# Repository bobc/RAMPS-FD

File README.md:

# RAMPS-FD

RAMPS for Due.

THIS IS THE DEVELOPMENT BRANCH.

Design files in the development branch are untested and not ready for manufacturing.

Status
-------

Nothing is ready for release yet!

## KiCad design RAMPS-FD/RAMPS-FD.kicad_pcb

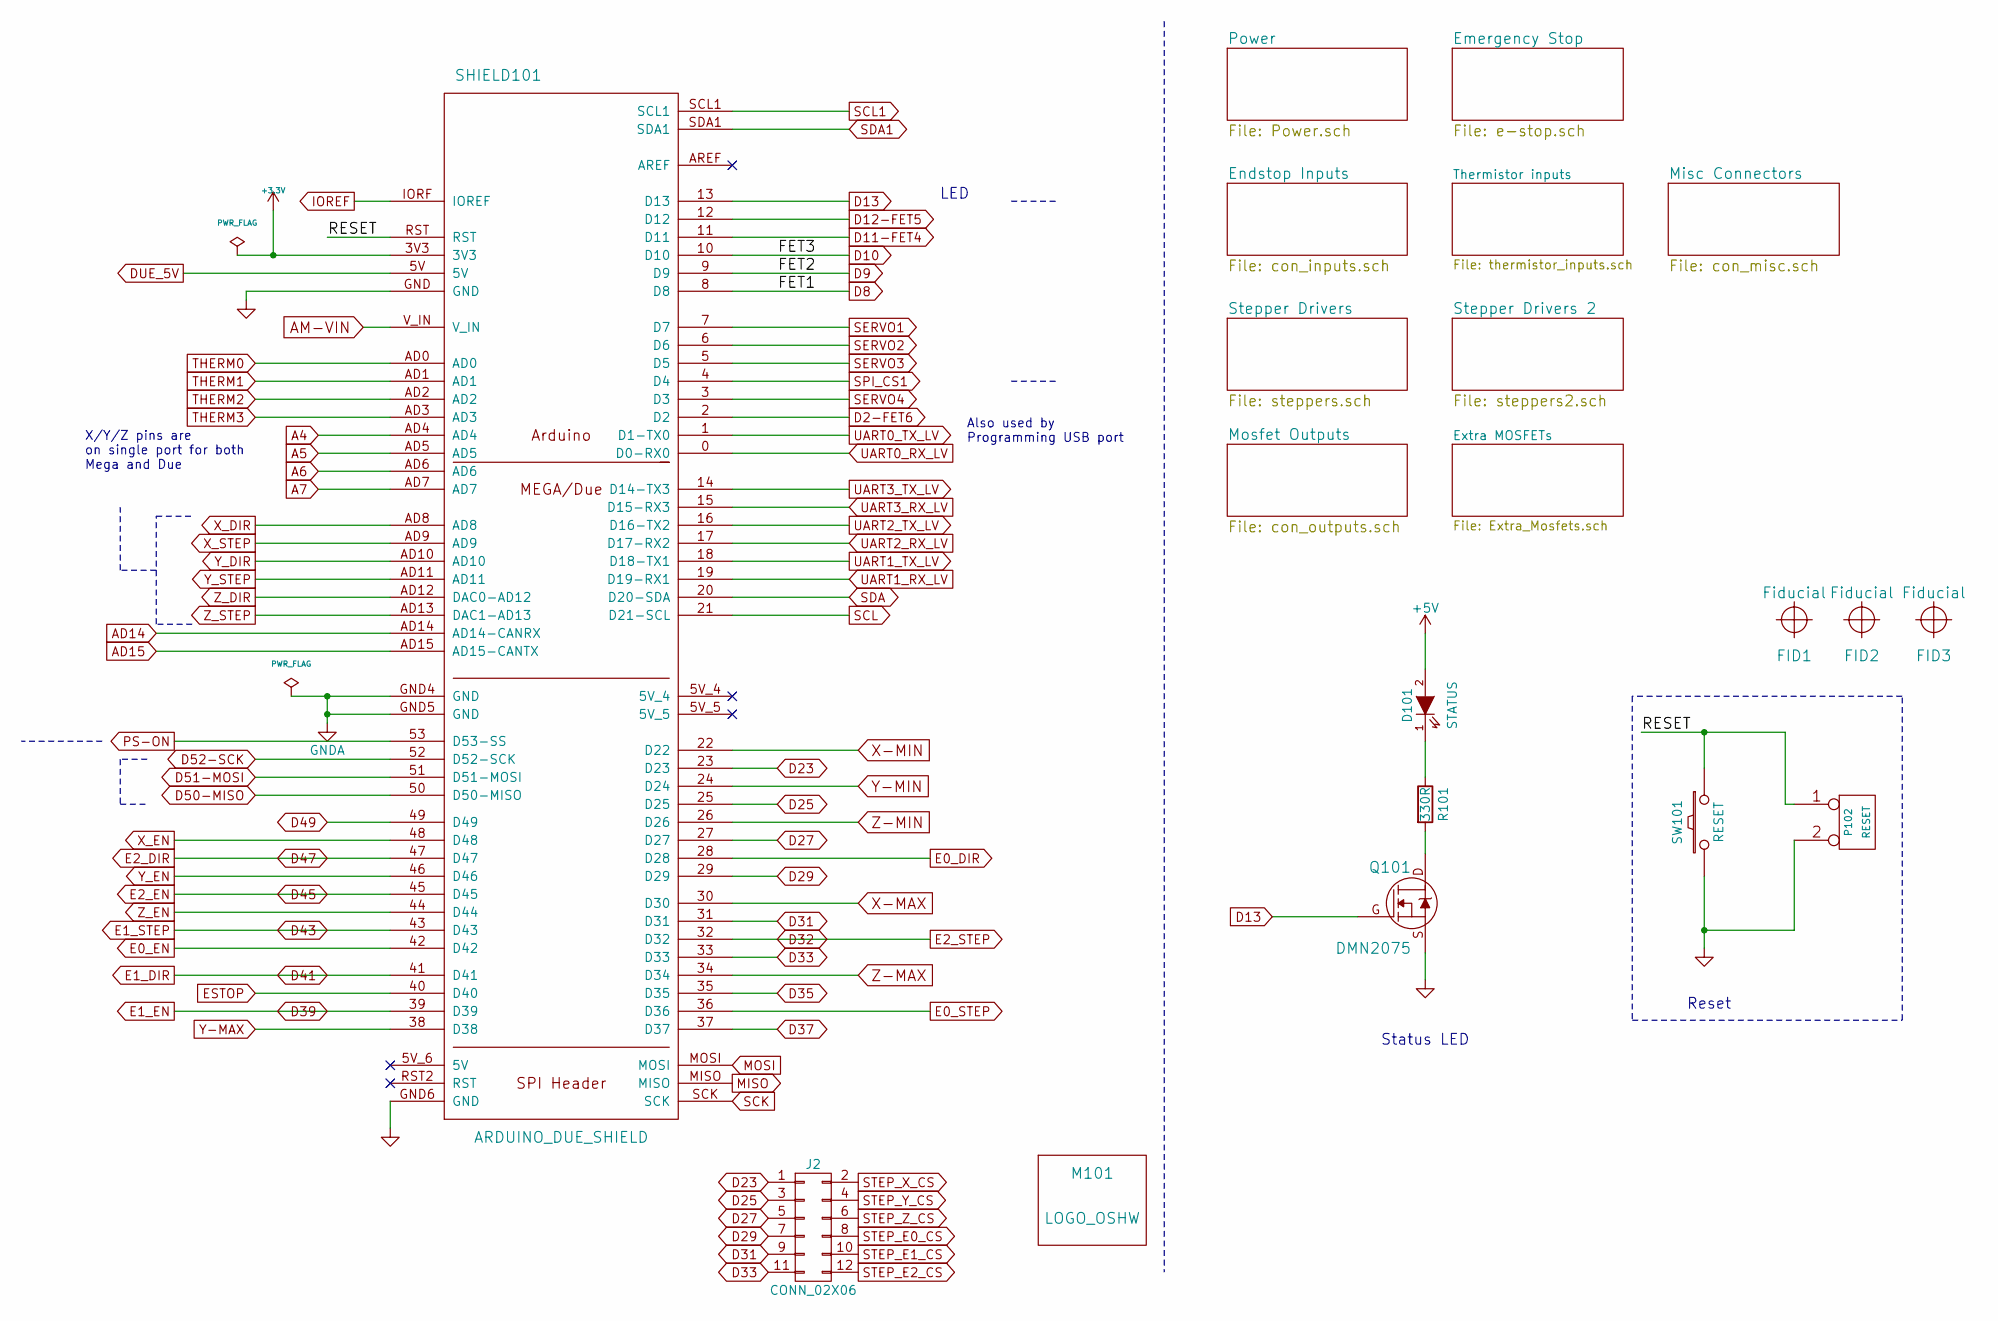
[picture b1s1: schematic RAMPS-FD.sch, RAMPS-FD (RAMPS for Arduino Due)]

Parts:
D101: STATUS; LED-0805_GREEN
FID1, FID2, FID3: Fiducial; Fiducial_1mm_Dia_2.54mm_Outer_CopperTop
J2: CONN_02X06; Pin_Header_Straight_2x06_Pitch2.54mm
M101: LOGO_OSHW; OSHW_logo_2
P102: RESET; Pin_Header_Straight_1x02_Pitch2.54mm
Q101: DMN2075; SOT23GDS
R101: 330R; R_0603
SHIELD101: ARDUINO_DUE_SHIELD; ARDUINO_MEGA_DUE_SHIELD_FOOTPRINT_RMC
SW101: RESET; SW_6x6_SMD

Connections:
+5V: D101.2 (A); also elsewhere on the board
/RESET: P102.1, SHIELD101.RST, SW101.1
A4: SHIELD101.AD4; also elsewhere on the board
A5: SHIELD101.AD5; also elsewhere on the board
A6: SHIELD101.AD6; also elsewhere on the board
A7: SHIELD101.AD7; also elsewhere on the board
AD14: SHIELD101.AD14 (AD14-CANRX); also elsewhere on the board
AD15: SHIELD101.AD15 (AD15-CANTX); also elsewhere on the board
AM-VIN: SHIELD101.V_IN; also elsewhere on the board
D2-FET6: SHIELD101.2 (D2); also elsewhere on the board
D8: SHIELD101.8 (D8); also elsewhere on the board
D9: SHIELD101.9 (D9); also elsewhere on the board
D10: SHIELD101.10 (D10); also elsewhere on the board
D11-FET4: SHIELD101.11 (D11); also elsewhere on the board
D12-FET5: SHIELD101.12 (D12); also elsewhere on the board
D13: Q101.G, SHIELD101.13 (D13)
D23: J2.1, SHIELD101.23 (D23); also elsewhere on the board
D25: J2.3, SHIELD101.25 (D25); also elsewhere on the board
D27: J2.5, SHIELD101.27 (D27); also elsewhere on the board
D29: J2.7, SHIELD101.29 (D29); also elsewhere on the board
D31: J2.9, SHIELD101.31 (D31); also elsewhere on the board
D32: SHIELD101.32 (D32); also elsewhere on the board
D33: J2.11, SHIELD101.33 (D33); also elsewhere on the board
D35: SHIELD101.35 (D35); also elsewhere on the board
D37: SHIELD101.37 (D37); also elsewhere on the board
D39: SHIELD101.39 (D39); also elsewhere on the board
D41: SHIELD101.41 (D41); also elsewhere on the board
D43: SHIELD101.43 (D43); also elsewhere on the board
D45: SHIELD101.45 (D45); also elsewhere on the board
D47: SHIELD101.47 (D47); also elsewhere on the board
D49: SHIELD101.49 (D49); also elsewhere on the board
D50-MISO: SHIELD101.50 (D50-MISO); also elsewhere on the board
D51-MOSI: SHIELD101.51 (D51-MOSI); also elsewhere on the board
D52-SCK: SHIELD101.52 (D52-SCK); also elsewhere on the board
DUE_5V: SHIELD101.5V; also elsewhere on the board
E0_DIR: SHIELD101.28 (D28); also elsewhere on the board
E0_EN: SHIELD101.42 (D42); also elsewhere on the board
E0_STEP: SHIELD101.36 (D36); also elsewhere on the board
ESTOP: SHIELD101.40 (D40); also elsewhere on the board
GND: P102.2 (PM), Q101.S, SHIELD101.GND, SHIELD101.GND6 (GND), SW101.2; also elsewhere on the board
GNDA: SHIELD101.GND4 (GND), SHIELD101.GND5 (GND); also elsewhere on the board
IOREF: SHIELD101.IORF (IOREF); also elsewhere on the board
MISO: SHIELD101.MISO; also elsewhere on the board
MOSI: SHIELD101.MOSI; also elsewhere on the board
unnamed: D101.1 (K), R101.1
unnamed: Q101.D, R101.2
PS-ON: SHIELD101.53 (D53-SS); also elsewhere on the board
SCK: SHIELD101.SCK; also elsewhere on the board
SCL: SHIELD101.21 (D21-SCL); also elsewhere on the board
SCL1: SHIELD101.SCL1; also elsewhere on the board
SDA: SHIELD101.20 (D20-SDA); also elsewhere on the board
SDA1: SHIELD101.SDA1; also elsewhere on the board
SERVO1: SHIELD101.7 (D7); also elsewhere on the board
SERVO2: SHIELD101.6 (D6); also elsewhere on the board
SERVO3: SHIELD101.5 (D5); also elsewhere on the board
SERVO4: SHIELD101.3 (D3); also elsewhere on the board
SPI_CS1: SHIELD101.4 (D4); also elsewhere on the board
THERM0: SHIELD101.AD0; also elsewhere on the board
THERM1: SHIELD101.AD1; also elsewhere on the board
THERM2: SHIELD101.AD2; also elsewhere on the board
THERM3: SHIELD101.AD3; also elsewhere on the board
UART0_RX_LV: SHIELD101.0 (D0-RX0); also elsewhere on the board
UART0_TX_LV: SHIELD101.1 (D1-TX0); also elsewhere on the board
UART1_RX_LV: SHIELD101.19 (D19-RX1); also elsewhere on the board
UART1_TX_LV: SHIELD101.18 (D18-TX1); also elsewhere on the board
UART2_RX_LV: SHIELD101.17 (D17-RX2); also elsewhere on the board
UART2_TX_LV: SHIELD101.16 (D16-TX2); also elsewhere on the board
UART3_RX_LV: SHIELD101.15 (D15-RX3); also elsewhere on the board
UART3_TX_LV: SHIELD101.14 (D14-TX3); also elsewhere on the board
X-MAX: SHIELD101.30 (D30); also elsewhere on the board
X-MIN: SHIELD101.22 (D22); also elsewhere on the board
X_DIR: SHIELD101.AD8; also elsewhere on the board
X_EN: SHIELD101.48 (D48); also elsewhere on the board
X_STEP: SHIELD101.AD9; also elsewhere on the board
Y-MAX: SHIELD101.38 (D38); also elsewhere on the board
Y-MIN: SHIELD101.24 (D24); also elsewhere on the board
Y_DIR: SHIELD101.AD10; also elsewhere on the board
Y_EN: SHIELD101.46 (D46); also elsewhere on the board
Y_STEP: SHIELD101.AD11; also elsewhere on the board
Z-MAX: SHIELD101.34 (D34); also elsewhere on the board
Z-MIN: SHIELD101.26 (D26); also elsewhere on the board
Z_DIR: SHIELD101.AD12 (DAC0-AD12); also elsewhere on the board
Z_EN: SHIELD101.44 (D44); also elsewhere on the board
Z_STEP: SHIELD101.AD13 (DAC1-AD13); also elsewhere on the board

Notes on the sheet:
Also used by Programming USB port
X/Y/Z pins are on single port for both Mega and Due
Reset
Status LED
LED

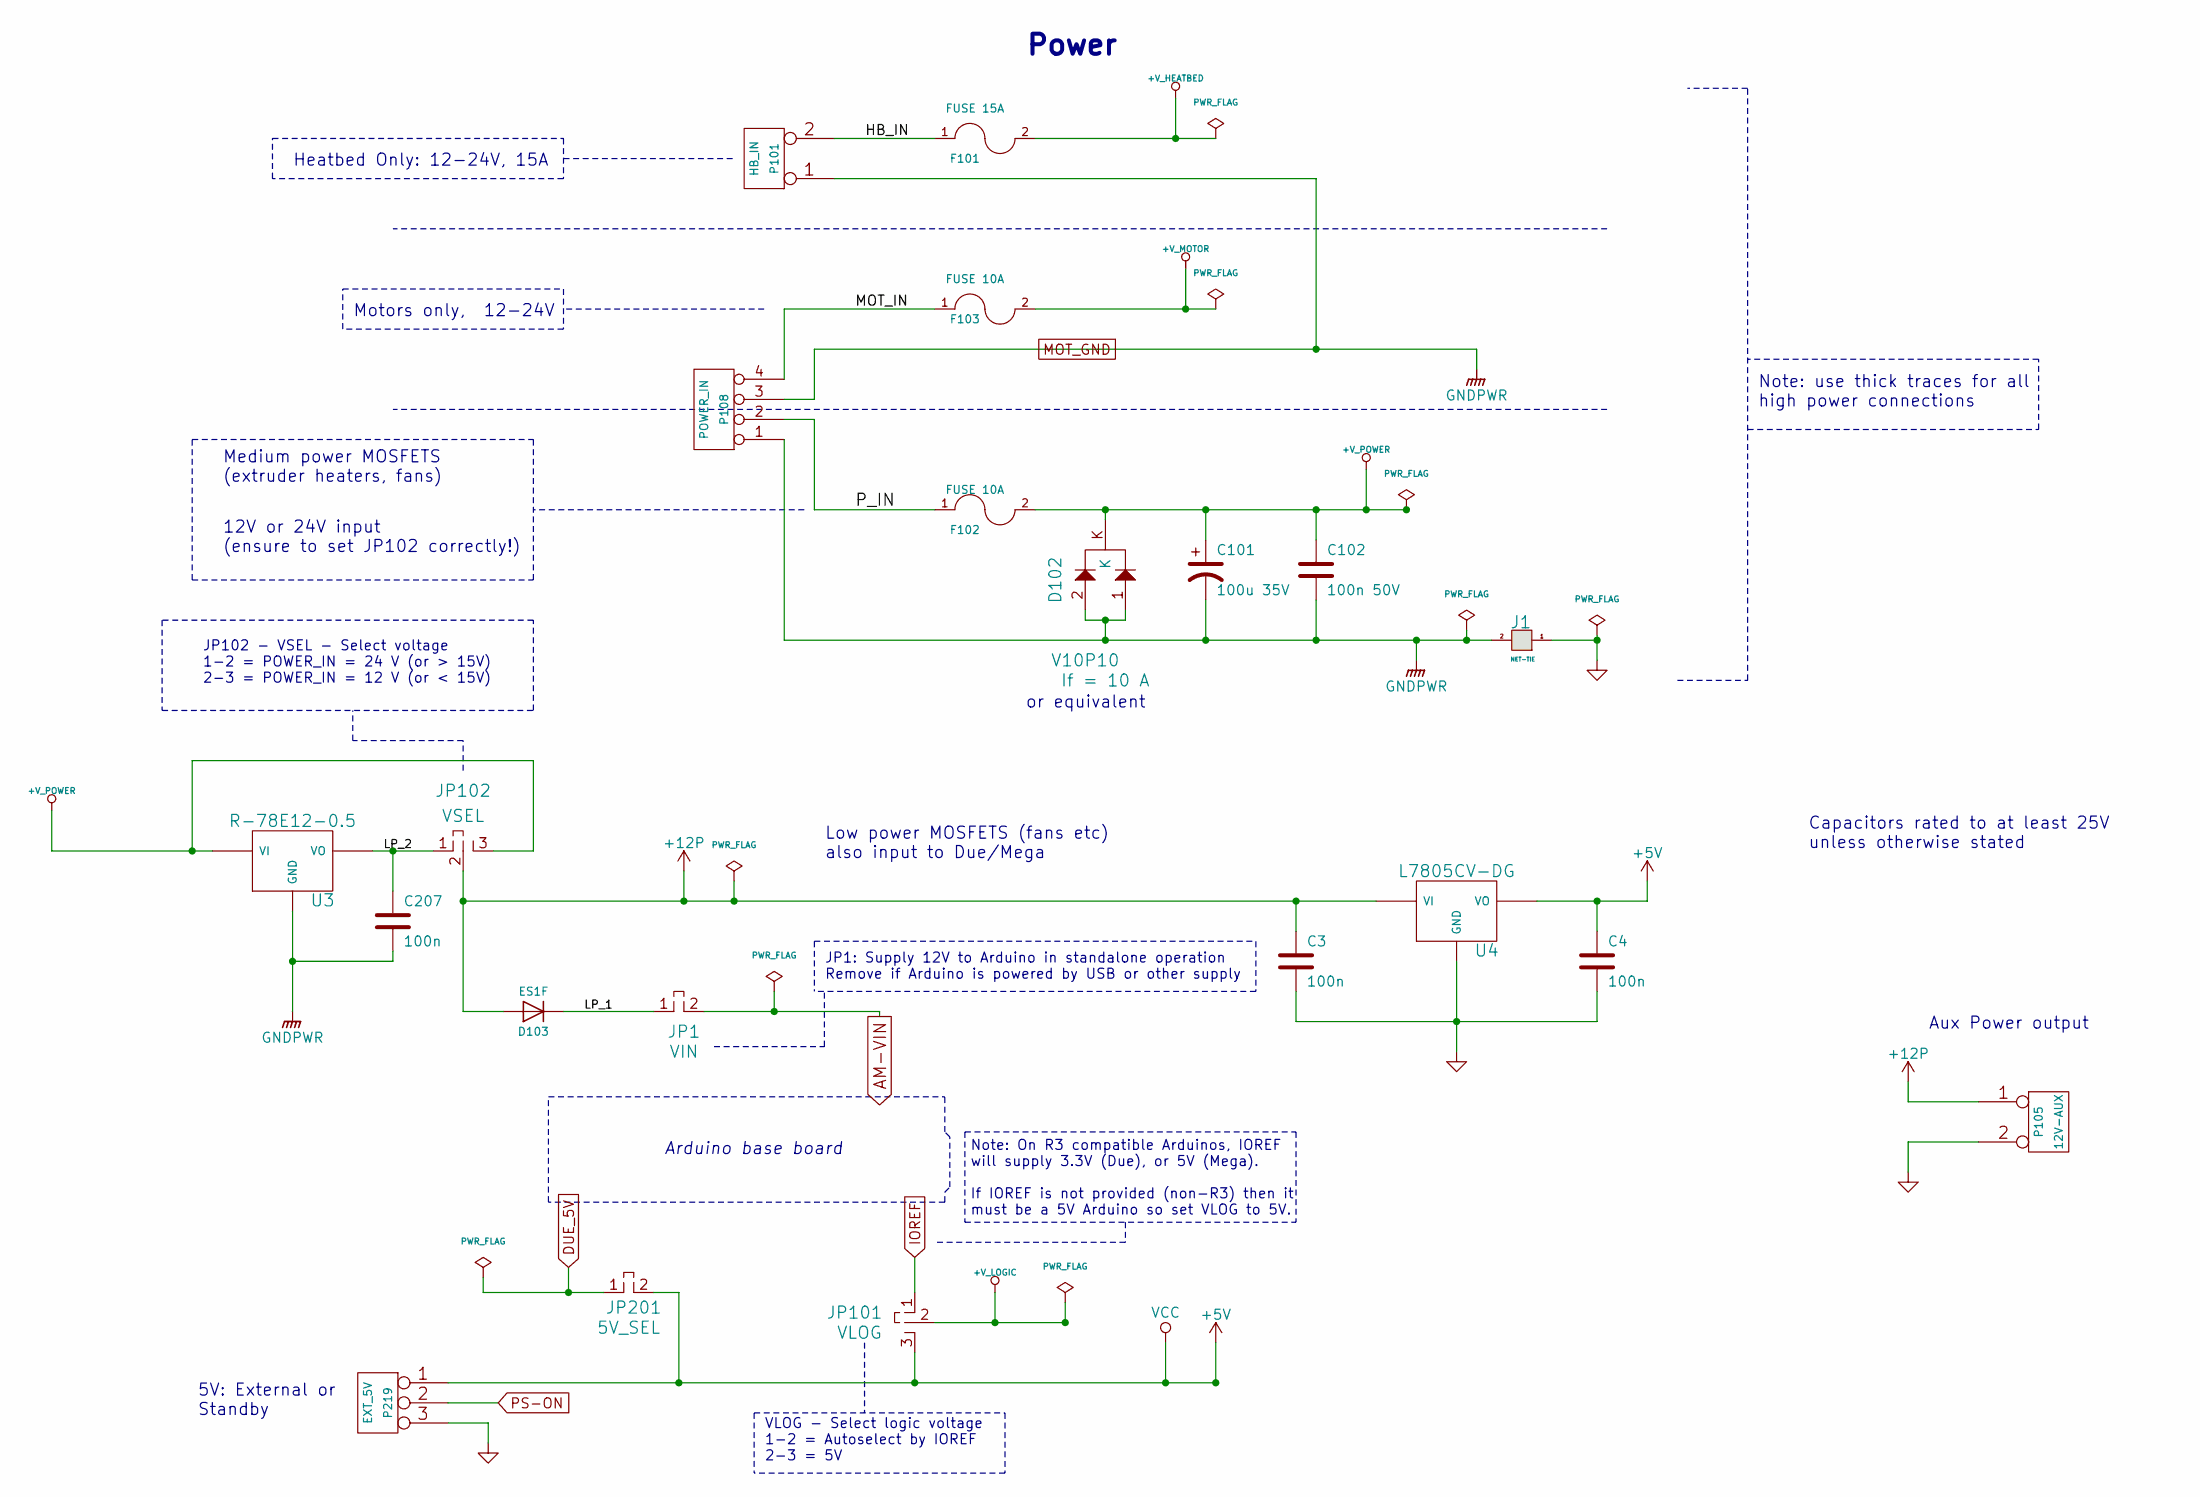
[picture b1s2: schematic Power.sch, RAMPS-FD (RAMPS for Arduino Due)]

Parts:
C3, C4, C207: 100n; C_0603
C101: 100u 35V; CP_Elec_6.3x7.7
C102: 100n 50V; C_0603
D102: V10P10; TO277A_RMC
D103: ES1F; DO-214AC
F101: FUSE 15A; Keystone_3568
F102, F103: FUSE 10A; Keystone_3568
J1: NET-TIE; TIE-1MM
JP1: VIN; Pin_Header_Straight_1x02_Pitch2.54mm
JP101: VLOG; Pin_Header_Straight_1x03_Pitch2.54mm
JP102: VSEL; Pin_Header_Straight_1x03_Pitch2.54mm
JP201: 5V_SEL; Pin_Header_Straight_1x02_Pitch2.54mm
P101: HB_IN; mstba_2,5%2f2-g-5,08
P105: 12V-AUX; CONN_KK_2.54_2W
P108: POWER_IN; mstba_2,5%2f4-g-5,08
P219: EXT_5V; CONN_KK_2.54_3W
U3: R-78E12-0.5; LM78XXV
U4: L7805CV-DG; LM78XXV

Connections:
+5V: C4.1, JP101.3, JP201.2, P219.1, U4.VO; also elsewhere on the board
+12P: C3.1, D103.2 (A), JP102.2, P105.1, U4.VI; also elsewhere on the board
+V_HEATBED: F101.2; also elsewhere on the board
+V_LOGIC: JP101.2; also elsewhere on the board
+V_MOTOR: F103.2; also elsewhere on the board
+V_POWER: C101.1, C102.1, D102.K, F102.2, JP102.3, U3.VI; also elsewhere on the board
/Power/HB_IN: F101.1, P101.2 (PM)
/Power/LP_1: D103.1 (K), JP1.1
/Power/LP_2: C207.1, JP102.1, U3.VO
/Power/MOT_IN: F103.1, P108.4
/Power/P_IN: F102.1, P108.2
AM-VIN: JP1.2; also elsewhere on the board
DUE_5V: JP201.1; also elsewhere on the board
GND: C3.2, C4.2, J1.1, P105.2 (PM), P219.3, U4.GND; also elsewhere on the board
IOREF: JP101.1; also elsewhere on the board
MOT_GND: C101.2, C102.2, C207.2, D102.1, D102.2, J1.2, P101.1, P108.1, P108.3, U3.GND; also elsewhere on the board
PS-ON: P219.2 (PM); also elsewhere on the board

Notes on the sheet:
JP102 - VSEL - Select voltage 1-2 = POWER_IN = 24 V (or > 15V) 2-3 = POWER_IN = 12 V (or < 15V)
Low power MOSFETS (fans etc) also input to Due/Mega
Aux Power output
VLOG - Select logic voltage 1-2 = Autoselect by IOREF 2-3 = 5V
Medium power MOSFETS (extruder heaters, fans)
Heatbed Only: 12-24V, 15A
Motors only, 12-24V
Power
JP1: Supply 12V to Arduino in standalone operation Remove if Arduino is powered by USB or other supply
Note: use thick traces for all high power connections
12V or 24V input (ensure to set JP102 correctly!)
5V: External or Standby
or equivalent
Arduino base board
Note: On R3 compatible Arduinos, IOREF will supply 3.3V (Due), or 5V (Mega). If IOREF is not provided (non-R3) then it must be a 5V Arduino so set VLOG to 5V.
Capacitors rated to at least 25V unless otherwise stated

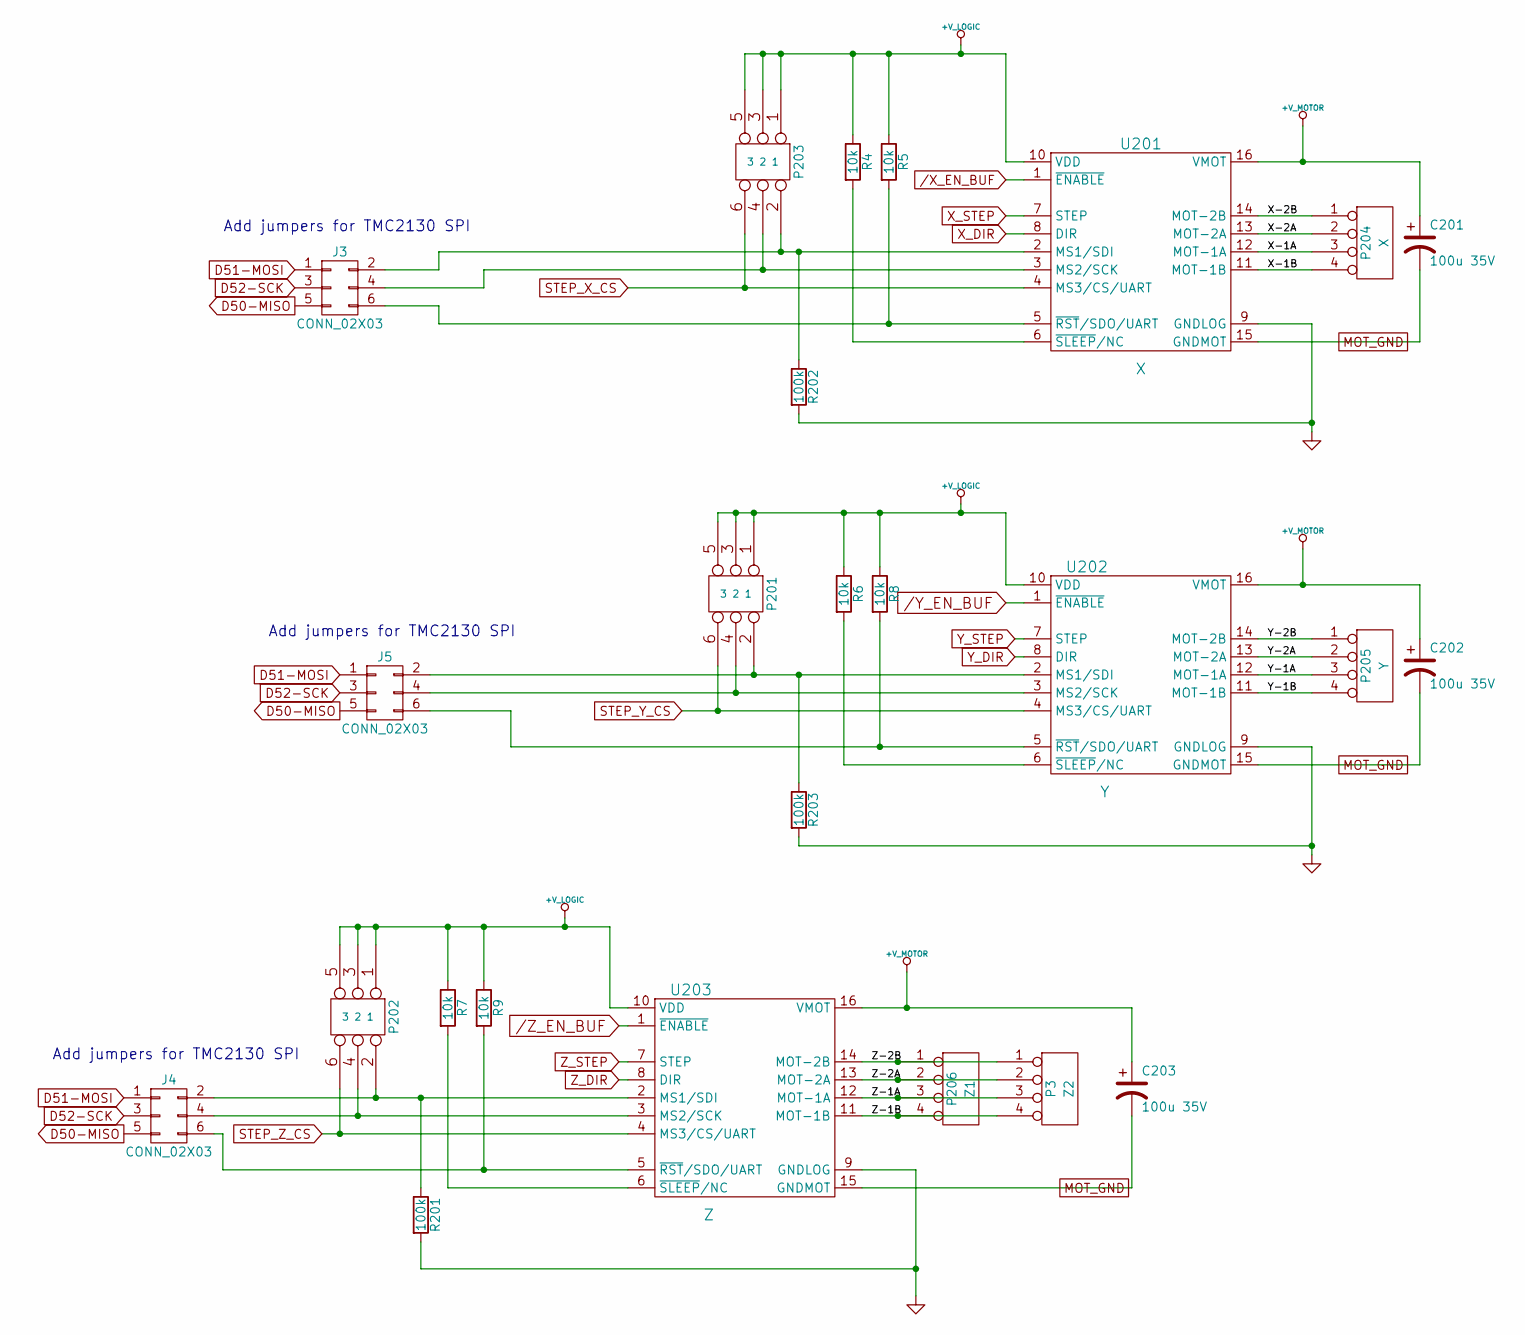
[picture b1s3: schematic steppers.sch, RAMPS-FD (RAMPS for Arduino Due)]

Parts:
C201, C202, C203: 100u 35V; CP_Elec_6.3x7.7
J3, J4, J5: CONN_02X03; Pin_Header_Straight_2x03_Pitch2.54mm
P3: Z2; CONN_KK_2.54_4W
P201, P202, P203: 3 2 1; Pin_Header_Straight_2x03_Pitch2.54mm
P204: X; CONN_KK_2.54_4W
P205: Y; CONN_KK_2.54_4W
P206: Z1; CONN_KK_2.54_4W
R4, R5, R6, R7, R8, R9: 10k; R_0603
R201, R202, R203: 100k; R_0603
U201: X; POLOLU
U202: Y; POLOLU
U203: Z; POLOLU

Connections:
+V_LOGIC: P201.1, P201.3, P201.5, P202.1, P202.3, P202.5, P203.1, P203.3, P203.5, R4.1, R5.1, R6.1, R7.1, R8.1, R9.1, U201.10 (VDD), U202.10 (VDD), U203.10 (VDD); also elsewhere on the board
+V_MOTOR: C201.1, C202.1, C203.1, U201.16 (VMOT), U202.16 (VMOT), U203.16 (VMOT); also elsewhere on the board
/Stepper Drivers/X-1A: P204.3, U201.12 (MOT-1A)
/Stepper Drivers/X-1B: P204.4, U201.11 (MOT-1B)
/Stepper Drivers/X-2A: P204.2, U201.13 (MOT-2A)
/Stepper Drivers/X-2B: P204.1, U201.14 (MOT-2B)
/Stepper Drivers/Y-1A: P205.3, U202.12 (MOT-1A)
/Stepper Drivers/Y-1B: P205.4, U202.11 (MOT-1B)
/Stepper Drivers/Y-2A: P205.2, U202.13 (MOT-2A)
/Stepper Drivers/Y-2B: P205.1, U202.14 (MOT-2B)
/Stepper Drivers/Z-1A: P3.3, P206.3, U203.12 (MOT-1A)
/Stepper Drivers/Z-1B: P3.4, P206.4, U203.11 (MOT-1B)
/Stepper Drivers/Z-2A: P3.2, P206.2, U203.13 (MOT-2A)
/Stepper Drivers/Z-2B: P3.1, P206.1, U203.14 (MOT-2B)
/X_EN_BUF: U201.1 (~ENABLE); also elsewhere on the board
/Y_EN_BUF: U202.1 (~ENABLE); also elsewhere on the board
/Z_EN_BUF: U203.1 (~ENABLE); also elsewhere on the board
GND: R201.2, R202.2, R203.2, U201.9 (GNDLOG), U202.9 (GNDLOG), U203.9 (GNDLOG); also elsewhere on the board
MOT_GND: C201.2, C202.2, C203.2, U201.15 (GNDMOT), U202.15 (GNDMOT), U203.15 (GNDMOT); also elsewhere on the board
unnamed: J3.1, J4.1, J5.1
unnamed: J3.2, P203.2, R202.1, U201.2 (MS1/SDI)
unnamed: J3.3, J4.3, J5.3
unnamed: J3.4, P203.4, U201.3 (MS2/SCK)
unnamed: J3.5, J4.5, J5.5
unnamed: J3.6, R5.2, U201.5 (~RST~/SDO/UART)
unnamed: J4.2, P202.2, R201.1, U203.2 (MS1/SDI)
unnamed: J4.4, P202.4, U203.3 (MS2/SCK)
unnamed: J4.6, R9.2, U203.5 (~RST~/SDO/UART)
unnamed: J5.2, P201.2, R203.1, U202.2 (MS1/SDI)
unnamed: J5.4, P201.4, U202.3 (MS2/SCK)
unnamed: J5.6, R8.2, U202.5 (~RST~/SDO/UART)
unnamed: R4.2, U201.6 (~SLEEP~/NC)
unnamed: R6.2, U202.6 (~SLEEP~/NC)
unnamed: R7.2, U203.6 (~SLEEP~/NC)
STEP_X_CS: P203.6, U201.4 (MS3/CS/UART)
STEP_Y_CS: P201.6, U202.4 (MS3/CS/UART)
STEP_Z_CS: P202.6, U203.4 (MS3/CS/UART)
X_DIR: U201.8 (DIR); also elsewhere on the board
X_STEP: U201.7 (STEP); also elsewhere on the board
Y_DIR: U202.8 (DIR); also elsewhere on the board
Y_STEP: U202.7 (STEP); also elsewhere on the board
Z_DIR: U203.8 (DIR); also elsewhere on the board
Z_STEP: U203.7 (STEP); also elsewhere on the board

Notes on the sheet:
Add jumpers for TMC2130 SPI

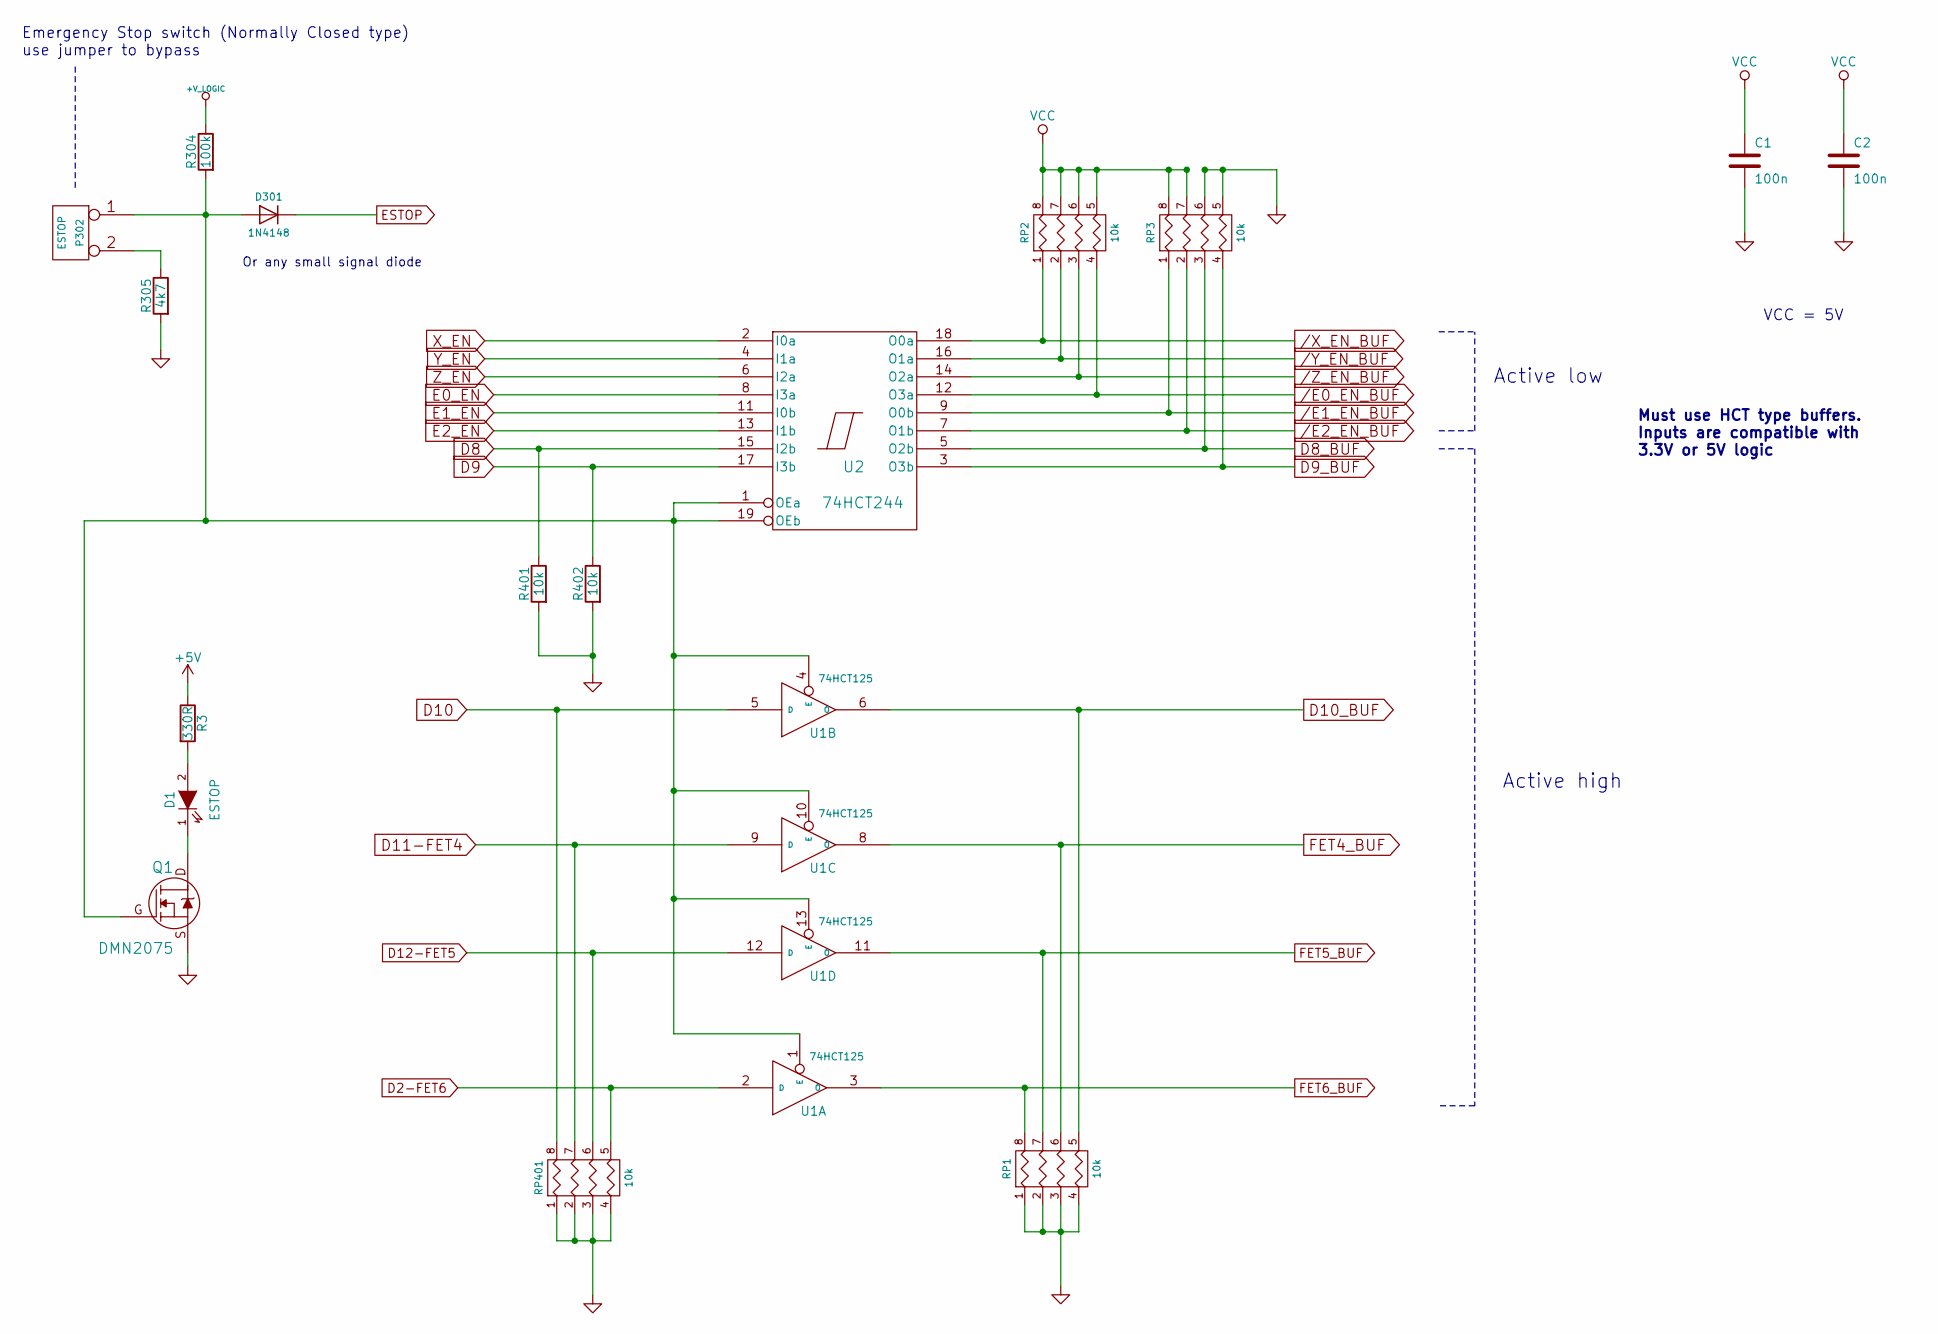
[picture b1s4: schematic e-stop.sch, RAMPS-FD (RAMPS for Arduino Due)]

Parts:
C1, C2: 100n; C_0603
D1: ESTOP; LED-0805_GREEN
D301: 1N4148; SOD-123
P302: ESTOP; CONN_KK_2.54_2W
Q1: DMN2075; SOT23GDS
R3: 330R; R_0603
R304: 100k; R_0603
R305: 4k7; R_0603
R401, R402: 10k; R_0603
RP1, RP2, RP3, RP401: 10k; R_Cat16-4
U1: 74HCT125; TSSOP-14_4.4x5mm_Pitch0.65mm
U2: 74HCT244; TSSOP-20_4.4x6.5mm_Pitch0.65mm

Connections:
+5V: C1.1, C2.1, R3.1, RP2.5 (R4), RP2.6 (R3), RP2.7 (R2), RP2.8 (R1), RP3.7 (R2), RP3.8 (R1), U1.14 (VCC), U2.20 (VCC); also elsewhere on the board
+V_LOGIC: R304.1; also elsewhere on the board
/E0_EN_BUF: RP2.4, U2.12 (O3a); also elsewhere on the board
/E1_EN_BUF: RP3.1, U2.9 (O0b); also elsewhere on the board
/E2_EN_BUF: RP3.2, U2.7 (O1b); also elsewhere on the board
/X_EN_BUF: RP2.1, U2.18 (O0a); also elsewhere on the board
/Y_EN_BUF: RP2.2, U2.16 (O1a); also elsewhere on the board
/Z_EN_BUF: RP2.3, U2.14 (O2a); also elsewhere on the board
D2-FET6: RP401.5 (R4), U1.2 (D); also elsewhere on the board
D8: R401.1, U2.15 (I2b); also elsewhere on the board
D8_BUF: RP3.3, U2.5 (O2b); also elsewhere on the board
D9: R402.1, U2.17 (I3b); also elsewhere on the board
D9_BUF: RP3.4, U2.3 (O3b); also elsewhere on the board
D10: RP401.8 (R1), U1.5 (D); also elsewhere on the board
D10_BUF: RP1.5 (R4), U1.6 (O); also elsewhere on the board
D11-FET4: RP401.7 (R2), U1.9 (D); also elsewhere on the board
D12-FET5: RP401.6 (R3), U1.12 (D); also elsewhere on the board
D39: U2.11 (I0b); also elsewhere on the board
D45: U2.13 (I1b); also elsewhere on the board
E0_EN: U2.8 (I3a); also elsewhere on the board
ESTOP: D301.1 (K); also elsewhere on the board
FET4_BUF: RP1.6 (R3), U1.8 (O); also elsewhere on the board
FET5_BUF: RP1.7 (R2), U1.11 (O); also elsewhere on the board
FET6_BUF: RP1.8 (R1), U1.3 (O); also elsewhere on the board
GND: C1.2, C2.2, Q1.S, R305.2, R401.2, R402.2, RP1.1, RP1.2, RP1.3, RP1.4, RP3.5 (R4), RP3.6 (R3), RP401.1, RP401.2, RP401.3, RP401.4, U1.7 (GND), U2.10 (GND); also elsewhere on the board
unnamed: D1.1 (K), Q1.D
unnamed: D1.2 (A), R3.2
unnamed: D301.2 (A), P302.1, Q1.G, R304.2, U1.1 (E), U1.4 (E), U1.10 (E), U1.13 (E), U2.1 (OEa), U2.19 (OEb)
unnamed: P302.2 (PM), R305.1
X_EN: U2.2 (I0a); also elsewhere on the board
Y_EN: U2.4 (I1a); also elsewhere on the board
Z_EN: U2.6 (I2a); also elsewhere on the board

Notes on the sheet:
Emergency Stop switch (Normally Closed type) use jumper to bypass
Or any small signal diode
Active low
Active high
VCC = 5V
Must use HCT type buffers. Inputs are compatible with 3.3V or 5V logic

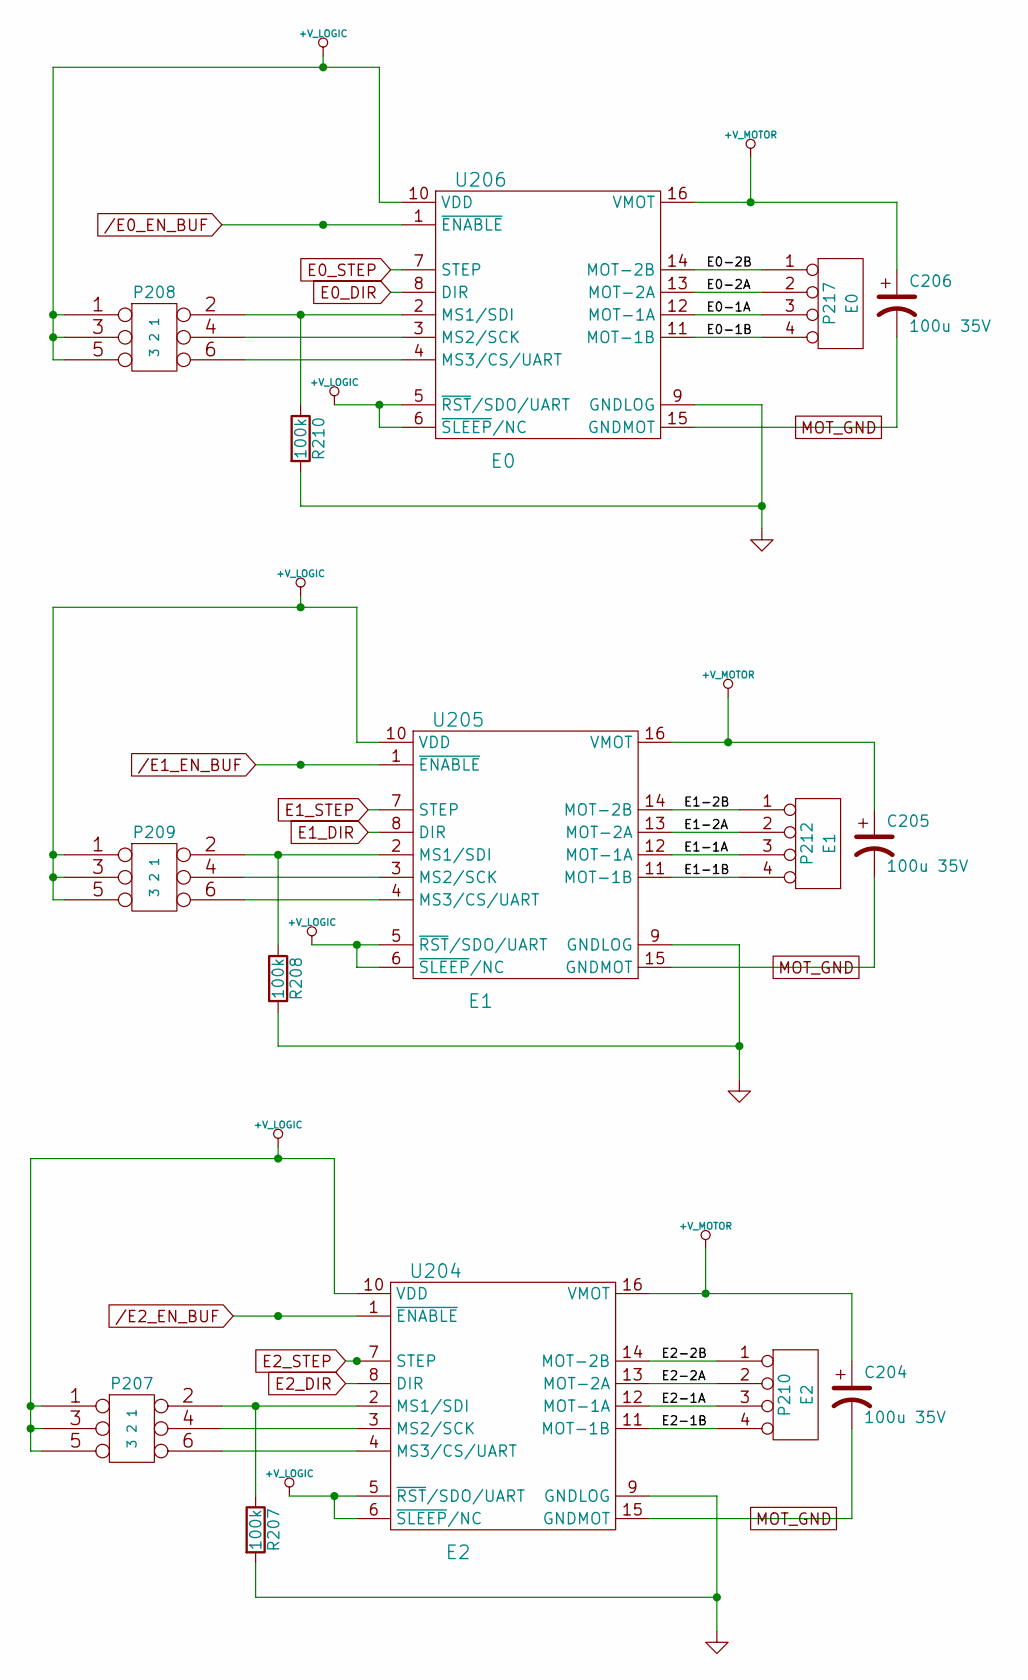
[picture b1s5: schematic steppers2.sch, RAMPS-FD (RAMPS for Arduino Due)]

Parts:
C204, C205, C206: 100u 35V; CP_Elec_6.3x7.7
P207, P208, P209: 3 2 1; Pin_Header_Straight_2x03_Pitch2.54mm
P210: E2; CONN_KK_2.54_4W
P212: E1; CONN_KK_2.54_4W
P217: E0; CONN_KK_2.54_4W
R207, R208, R210: 100k; R_0603
U204: E2; POLOLU
U205: E1; POLOLU
U206: E0; POLOLU

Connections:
+V_LOGIC: P207.1, P207.3, P207.5, P208.1, P208.3, P208.5, P209.1, P209.3, P209.5, U204.5 (~RST~/SDO/UART), U204.6 (~SLEEP~/NC), U204.10 (VDD), U205.5 (~RST~/SDO/UART), U205.6 (~SLEEP~/NC), U205.10 (VDD), U206.5 (~RST~/SDO/UART), U206.6 (~SLEEP~/NC), U206.10 (VDD); also elsewhere on the board
+V_MOTOR: C204.1, C205.1, C206.1, U204.16 (VMOT), U205.16 (VMOT), U206.16 (VMOT); also elsewhere on the board
/E0_EN_BUF: U206.1 (~ENABLE); also elsewhere on the board
/E1_EN_BUF: U205.1 (~ENABLE); also elsewhere on the board
/E2_EN_BUF: U204.1 (~ENABLE); also elsewhere on the board
/Stepper Drivers 2/E0-1A: P217.3, U206.12 (MOT-1A)
/Stepper Drivers 2/E0-1B: P217.4, U206.11 (MOT-1B)
/Stepper Drivers 2/E0-2A: P217.2, U206.13 (MOT-2A)
/Stepper Drivers 2/E0-2B: P217.1, U206.14 (MOT-2B)
/Stepper Drivers 2/E1-1A: P212.3, U205.12 (MOT-1A)
/Stepper Drivers 2/E1-1B: P212.4, U205.11 (MOT-1B)
/Stepper Drivers 2/E1-2A: P212.2, U205.13 (MOT-2A)
/Stepper Drivers 2/E1-2B: P212.1, U205.14 (MOT-2B)
/Stepper Drivers 2/E2-1A: P210.3, U204.12 (MOT-1A)
/Stepper Drivers 2/E2-1B: P210.4, U204.11 (MOT-1B)
/Stepper Drivers 2/E2-2A: P210.2, U204.13 (MOT-2A)
/Stepper Drivers 2/E2-2B: P210.1, U204.14 (MOT-2B)
D32: U204.7 (STEP); also elsewhere on the board
D41: U205.8 (DIR); also elsewhere on the board
D43: U205.7 (STEP); also elsewhere on the board
D47: U204.8 (DIR); also elsewhere on the board
E0_DIR: U206.8 (DIR); also elsewhere on the board
E0_STEP: U206.7 (STEP); also elsewhere on the board
GND: R207.2, R208.2, R210.2, U204.9 (GNDLOG), U205.9 (GNDLOG), U206.9 (GNDLOG); also elsewhere on the board
MOT_GND: C204.2, C205.2, C206.2, U204.15 (GNDMOT), U205.15 (GNDMOT), U206.15 (GNDMOT); also elsewhere on the board
unnamed: P207.2, R207.1, U204.2 (MS1/SDI)
unnamed: P207.4, U204.3 (MS2/SCK)
unnamed: P207.6, U204.4 (MS3/CS/UART)
unnamed: P208.2, R210.1, U206.2 (MS1/SDI)
unnamed: P208.4, U206.3 (MS2/SCK)
unnamed: P208.6, U206.4 (MS3/CS/UART)
unnamed: P209.2, R208.1, U205.2 (MS1/SDI)
unnamed: P209.4, U205.3 (MS2/SCK)
unnamed: P209.6, U205.4 (MS3/CS/UART)

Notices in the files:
RAMPS-FD/Extra_Mosfets.sch:
GPL v3
